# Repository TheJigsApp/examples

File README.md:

# TheJigsApp Examples
## Collection of example jig design packages with outputs
These are recommended as starting points and references for designing your own custom bed-of-nails production, development, or hardware-in-the-loop jig.

## Glasgow
+ [Glasgow Embedded: glasgow](glasgow)
+ [Source](https://github.com/GlasgowEmbedded/glasgow)

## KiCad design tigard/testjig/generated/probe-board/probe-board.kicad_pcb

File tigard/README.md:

# Securing Hardware: Tigard
## 2024-07-13

+ [Store: Crowd Supply](https://www.crowdsupply.com/securinghw/tigard)
+ [Store: Mouser](https://www.mouser.com/ProductDetail/Securing-Hardware/TIGARD-V1)
+ [Company Website](https://securinghardware.com/)
+ [Source: GitHub](https://github.com/tigard-tools/tigard)

## Building Input Package
1. Package the manufacturing files
  ```sh
  make -f ../libs/kicad-make/Makefile --directory=tigard OUTDIR=$(pwd)/testjig PROJECT=tigard VERSION=1.1.X 
  ```
This will create a zip with the gerbers (and other manufacturing drawings)

2. Export the test-point report
  ```sh
  kicad_testpoints by-fab-setting --pcb tigard.kicad_pcb  --out $(pwd)/testjig/testpoint-report.xlsx --drill-center 
  ```

3. Create the design.toml file
  + The web interface will give feedback on these values with visualizaions

4. Create the design-input.xlsx file
  + Paste in the test-point report
  + Add Support pins
  + Assign nets to the connector

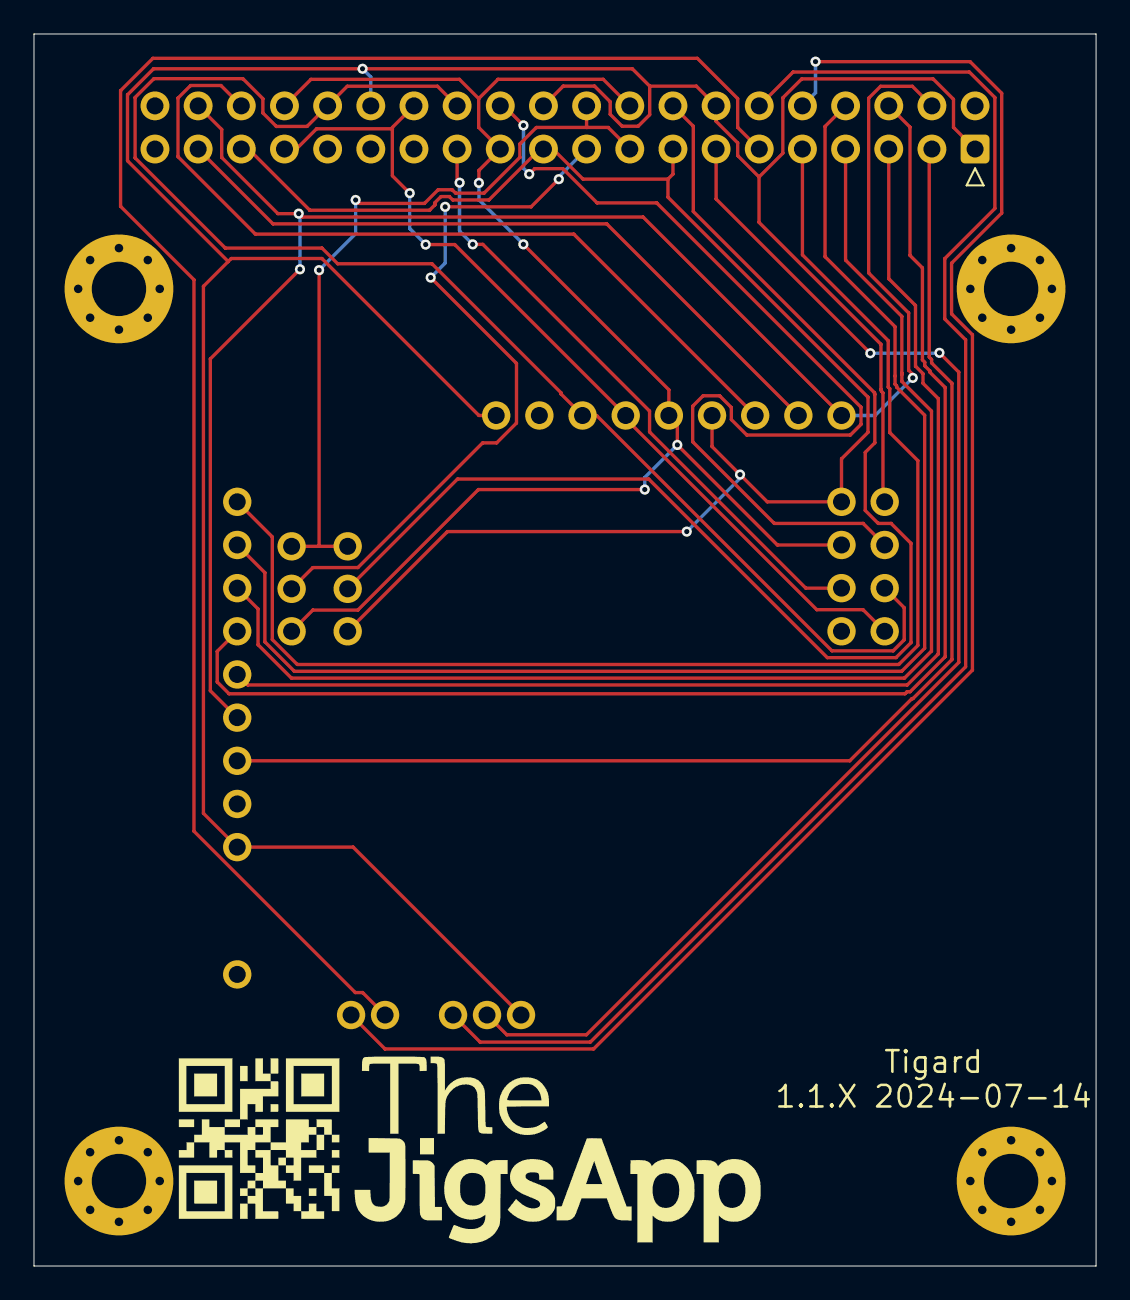
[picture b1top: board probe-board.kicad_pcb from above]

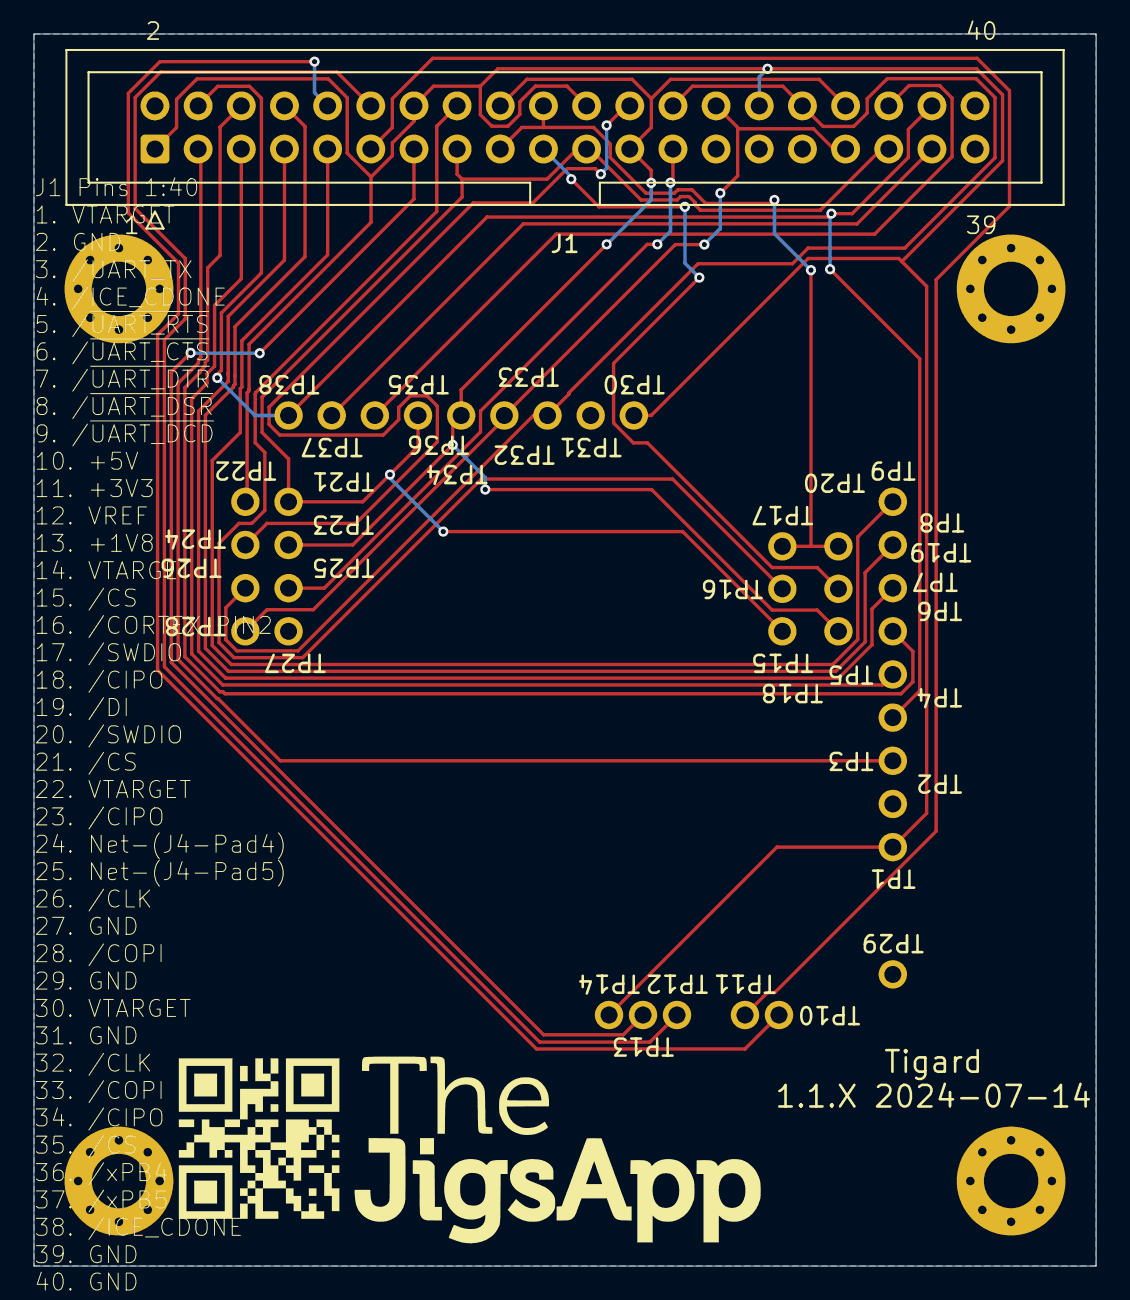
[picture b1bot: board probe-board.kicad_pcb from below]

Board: 2 copper layers, 62.5 x 72.5 mm, 48 parts (41 on the bottom side), 24 nets.

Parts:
BOARD: BOARD; tmpw_hl84_g
J1: Connector; IDC-Header_2x20_P2.54mm_Vertical
LOGO1, LOGO2: LOGO; TJA-SS-24x11
MH1, MH2, MH3, MH4: M3; MountingHole_3.2mm_M3_Pad_Via_Paste
QR1, QR2: QR; tmp3uzne9rn
TP1: TP1; R100-2W
TP2: TP2; R100-2W
TP3: TP3; R100-2W
TP4: TP4; R100-2W
TP5: TP5; R100-2W
TP6: TP6; R100-2W
TP7: TP7; R100-2W
TP8: TP8; R100-2W
TP9: TP9; R100-2W
TP10: TP10; R100-2W
TP11: TP11; R100-2W
TP12: TP12; R100-2W
TP13: TP13; R100-2W
TP14: TP14; R100-2W
TP15: TP15; R100-2W
TP16: TP16; R100-2W
TP17: TP17; R100-2W
TP18: TP18; R100-2W
TP19: TP19; R100-2W
TP20: TP20; R100-2W
TP21: TP21; R100-2W
TP22: TP22; R100-2W
TP23: TP23; R100-2W
TP24: TP24; R100-2W
TP25: TP25; R100-2W
TP26: TP26; R100-2W
TP27: TP27; R100-2W
TP28: TP28; R100-2W
TP29: TP29; R100-2W
TP30: TP30; R100-2W
TP31: TP31; R100-2W
TP32: TP32; R100-2W
TP33: TP33; R100-2W
TP34: TP34; R100-2W
TP35: TP35; R100-2W
TP36: TP36; R100-2W
TP37: TP37; R100-2W
TP38: TP38; R100-2W

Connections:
+1V8: J1.13, TP13.1
+3V3: J1.11, TP11.1
+5V: J1.10, TP10.1
/CIPO: J1.18, J1.23, J1.34, TP18.1, TP23.1, TP34.1
/CLK: J1.26, J1.32, TP26.1, TP32.1
/COPI: J1.28, J1.33, TP28.1, TP33.1
/CORTEX_PIN2: J1.16, TP16.1
/CS: J1.15, J1.21, J1.35, TP15.1, TP21.1, TP35.1
/DI: J1.19, TP19.1
/ICE_CDONE: J1.4, J1.38, TP4.1, TP38.1
/SWDIO: J1.17, J1.20, TP17.1, TP20.1
/UART_TX: J1.3, TP3.1
/xPB4: J1.36, TP36.1
/xPB5: J1.37, TP37.1
/~UART_CTS: J1.6, TP6.1
/~UART_DCD: J1.9, TP9.1
/~UART_DSR: J1.8, TP8.1
/~UART_DTR: J1.7, TP7.1
/~UART_RTS: J1.5, TP5.1
GND: J1.2, J1.27, J1.29, J1.31, J1.39, J1.40, MH1.1, MH2.1, MH3.1, MH4.1, TP2.1, TP27.1, TP29.1, TP31.1
unnamed: J1.24, TP24.1
unnamed: J1.25, TP25.1
VREF: J1.12, TP12.1
VTARGET: J1.1, J1.14, J1.22, J1.30, TP1.1, TP14.1, TP22.1, TP30.1

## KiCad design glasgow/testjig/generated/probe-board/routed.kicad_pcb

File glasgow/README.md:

# GlasgowEmbedded: Glasgow
## 2024-07-13

## Building Input Package
1. Package the manufacturing files
  ```sh
  make -f ../libs/kicad-make/Makefile --directory=glasgow/hardware/boards/glasgow OUTDIR=$(pwd)/testjig PROJECT=glasgow VERSION=C.1.X 
  ```
This will create a zip with the gerbers (and other manufacturing drawings)

2. Export the test-point report
  ```sh
  kicad_testpoints by-fab-setting --pcb glasgow/hardware/boards/glasgow/glasgow.kicad_pcb  --out $(pwd)/testjig/testpoint-report.xlsx --drill-center 
  ```

3. Create the design.toml file
  + The web interface will give feedback on these values with visualizaions

4. Create the design-input.xlsx file
  + Paste in the test-point report
  + Add Support pins
  + Assign nets to the connector

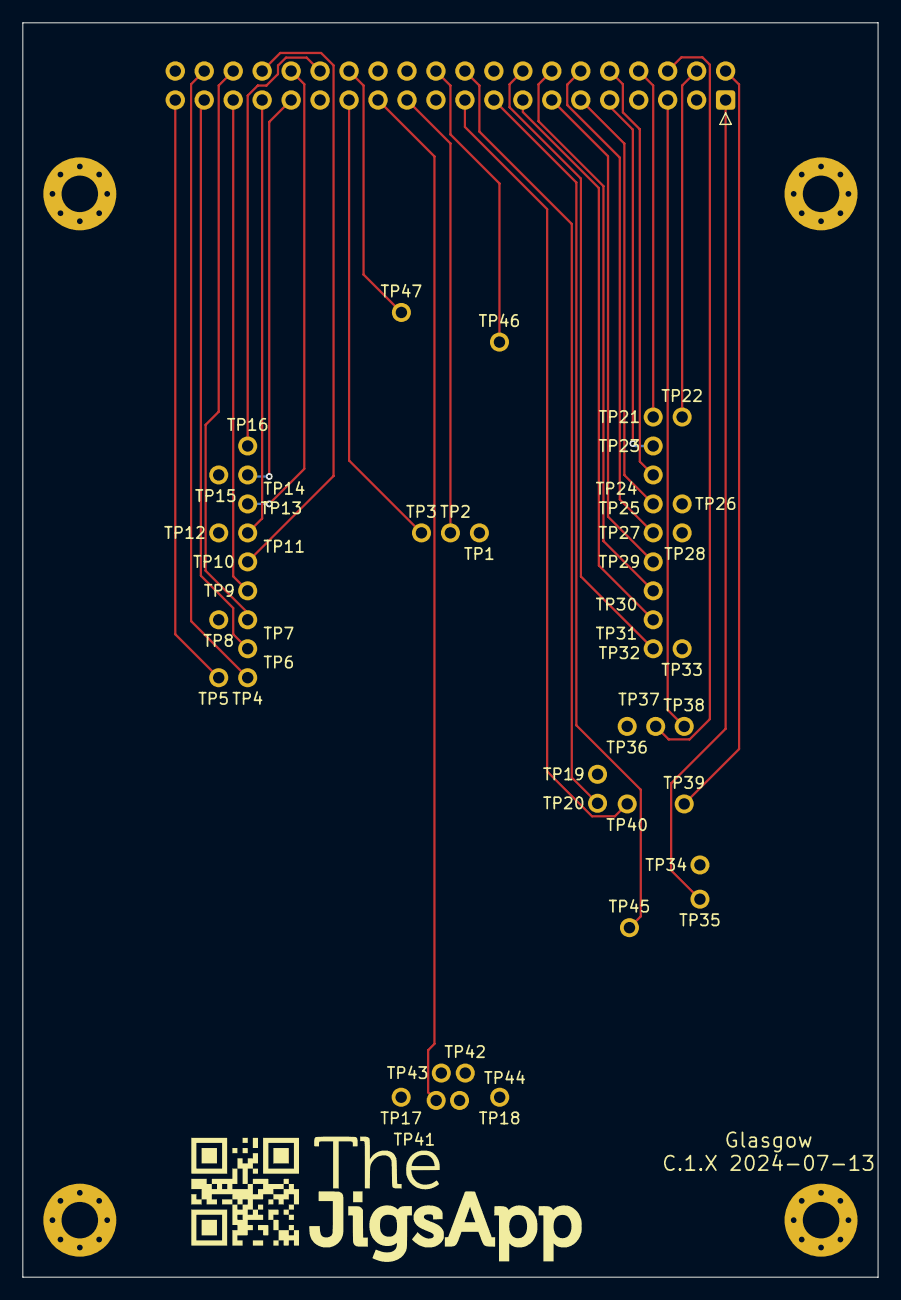
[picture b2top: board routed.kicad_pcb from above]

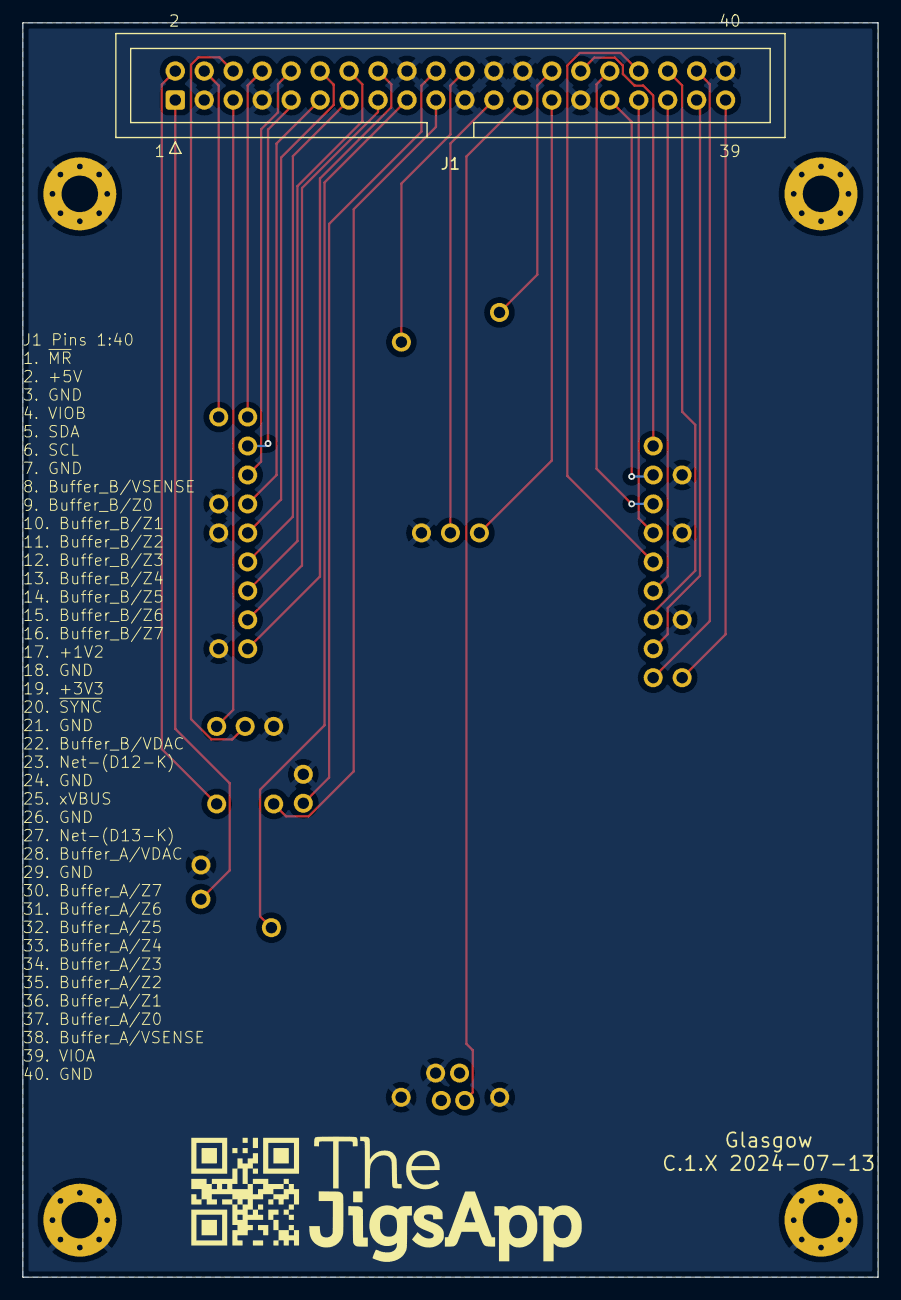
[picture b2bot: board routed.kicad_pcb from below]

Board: 2 copper layers, 75.0 x 110.0 mm, 57 parts (3 on the bottom side), 33 nets.

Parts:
BOARD: BOARD; tmp9db8qn8v
J1: Connector; IDC-Header_2x20_P2.54mm_Vertical
LOGO1, LOGO2: LOGO; TJA-SS-24x11
MH1, MH2, MH3, MH4: M3; MountingHole_3.2mm_M3_Pad_Via_Paste
QR1, QR2: QR; tmpb78doxsu
TP1: TP1; R100-2W
TP2: TP2; R100-2W
TP3: TP3; R100-2W
TP4: TP4; R100-2W
TP5: TP5; R100-2W
TP6: TP6; R100-2W
TP7: TP7; R100-2W
TP8: TP8; R100-2W
TP9: TP9; R100-2W
TP10: TP10; R100-2W
TP11: TP11; R100-2W
TP12: TP12; R100-2W
TP13: TP13; R100-2W
TP14: TP14; R100-2W
TP15: TP15; R100-2W
TP16: TP16; R100-2W
TP17: TP17; R100-2W
TP18: TP18; R100-2W
TP19: TP19; R100-2W
TP20: TP20; R100-2W
TP21: TP21; R100-2W
TP22: TP22; R100-2W
TP23: TP23; R100-2W
TP24: TP24; R100-2W
TP25: TP25; R100-2W
TP26: TP26; R100-2W
TP27: TP27; R100-2W
TP28: TP28; R100-2W
TP29: TP29; R100-2W
TP30: TP30; R100-2W
TP31: TP31; R100-2W
TP32: TP32; R100-2W
TP33: TP33; R100-2W
TP34: TP34; R100-2W
TP35: TP35; R100-2W
TP36: TP36; R100-2W
TP37: TP37; R100-2W
TP38: TP38; R100-2W
TP39: TP39; R100-2W
TP40: TP40; R100-2W
TP41: TP41; R100-2W
TP42: TP42; R100-2W
TP43: TP43; R100-2W
TP44: TP44; R100-2W
TP45: TP45; R100-2W
TP46: TP46; R100-2W
TP47: TP47; R100-2W

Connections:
+1V2: J1.17, TP45.1
+3V3: J1.19, TP40.1
+5V: J1.2, TP39.1
Buffer_A/VDAC: J1.28, TP47.1
Buffer_A/VSENSE: J1.38, TP4.1
Buffer_A/Z0: J1.37, TP6.1
Buffer_A/Z1: J1.36, TP7.1
Buffer_A/Z2: J1.35, TP9.1
Buffer_A/Z3: J1.34, TP10.1
Buffer_A/Z4: J1.33, TP11.1
Buffer_A/Z5: J1.32, TP13.1
Buffer_A/Z6: J1.31, TP14.1
Buffer_A/Z7: J1.30, TP16.1
Buffer_B/VDAC: J1.22, TP46.1
Buffer_B/VSENSE: J1.8, TP21.1
Buffer_B/Z0: J1.9, TP23.1
Buffer_B/Z1: J1.10, TP24.1
Buffer_B/Z2: J1.11, TP25.1
Buffer_B/Z3: J1.12, TP27.1
Buffer_B/Z4: J1.13, TP29.1
Buffer_B/Z5: J1.14, TP30.1
Buffer_B/Z6: J1.15, TP31.1
Buffer_B/Z7: J1.16, TP32.1
GND: J1.3, J1.7, J1.18, J1.21, J1.24, J1.26, J1.29, J1.40, MH1.1, MH2.1, MH3.1, MH4.1, TP1.1, TP8.1, TP12.1, TP15.1, TP17.1, TP18.1, TP19.1, TP26.1, TP28.1, TP33.1, TP34.1, TP36.1, TP42.1
unnamed: J1.23, TP2.1
unnamed: J1.27, TP3.1
SCL: J1.6, TP37.1
SDA: J1.5, TP38.1
VIOA: J1.39, TP5.1
VIOB: J1.4, TP22.1
xVBUS: J1.25, TP41.1
~MR: J1.1, TP35.1
~SYNC: J1.20, TP20.1

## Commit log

2024-07-13 adding glasgow
2024-07-13 updating jig type for glagow
2024-07-14 adding images
2024-07-14 adding renders
2024-07-14 updating labels on glasgow
2024-07-14 updating glasgow example renders
2024-07-14 tigard updates
2024-07-14 adding tigard
2024-07-14 adding prusa
2024-07-14 moving support
2024-07-16 adding librem5
2024-07-16 adding beagle bone
2024-07-16 updating beaglebone
2024-09-27 adding mobo
2025-07-28 updating examples
2025-07-29 adding templates
